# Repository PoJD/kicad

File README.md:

# kicad

Printed circuit boards. A container for all projects, successor to the older
`eagle` repo.

KiCad 10 — text formats, readable diffs, ERC and DRC running in CI through
`kicad-cli` without a GUI. The CI container image tracks the local major
version, because KiCad refuses to open files written by a newer one.

## Boards

| Board | Status | Description |
|---|---|---|
| [`canfuel/`](canfuel/) | design finished, `fab/` generated | fuel consumption converter for a VW PQ34 car, powered from the display it feeds |

The `canfuel` board is finished: schematic and PCB complete, ERC and DRC clean
with zero unconnected items, 24 parts on 55 × 45 mm and two layers, `fab/`
generated and committed. ⚠ **While a fabrication order is outstanding, do not
edit the board files** — `fab/` describes the commit that was sent, and an edit
makes it stop describing what is being made.

The harness is built, fitted and measured —
[`canfuel/docs/harness.md`](canfuel/docs/harness.md) is the procedure. **The
whole build path, across all three repositories, is
[`canfuel/docs/firmware/install.md`](https://github.com/PoJD/canfuel/blob/main/docs/firmware/install.md);**
the steps this repository owns are the board and the loom.

## Prerequisites

| For | What | Notes |
|---|---|---|
| opening and editing | **KiCad 10.x** | the **major** version matters, see below |
| the checks | **`kicad-cli`** | installed with KiCad, no separate download |
| `tools/check-*.py` | **Python 3** | no third-party packages |

```
kicad-cli version          # must print 10.x
```

**The major version is not a preference.** KiCad refuses to open files written
by a newer major version, so a mismatch is a hard failure rather than a
warning. CI runs the `kicad/kicad:10.0` container image and that image tracks
whatever is installed locally — bump the two together, never separately.

Nothing here needs a licence, an account or a plugin. Making the board also
needs no KiCad at all: `fab/` is generated and committed, so a fab house can be
given those files directly.

## Layout

```
lib/                symbols and footprints shared across projects
<board>/
  *.kicad_pro       project
  *.kicad_sch       schematic
  *.kicad_pcb       board
  fab/              gerbers, BOM, CPL — committed
  docs/             design documents, datasheets, and how to build the harness
```

For the `canfuel` board specifically, `canfuel/docs/` holds:

| File | Contents |
|---|---|
| `harness.md` | **making the loom and wiring it into the car** — a checklist, with the crimping, the connector cavities and the fuse |
| `pinout.md` | one-page reference for all three connectors |
| `harness-*.svg` | the connector and the four nets drawn from the real pad coordinates in `canfuel.kicad_pcb`, so they cannot disagree with the board |
| `assembly-orientation.svg` | **the figure to have open while soldering** — both sides of the board, and which way round each of the five parts that can go in backwards goes |
| `solder-check.md` | **after each joint** — for every pad on the board, where the meter must read zero and what it must stay open to, with the gap in millimetres |
| `implementation-plan.md` | how the board was designed, every number cited to a datasheet |
| `*.pdf` | the manufacturers' datasheets, listed in `NOTICE` as theirs |

`*.kicad_prl` is local state and does not belong in the repo (it is gitignored).

`fab/` is committed deliberately even though it is generated: for any board
that has been ordered it must be possible to find out exactly what was sent to
the fab.

## CI

`kicad-cli sch erc` and `kicad-cli pcb drc`. Both must pass before boards are
ordered. The workflow **fails if it finds no design files**, so a green run
always means something was actually opened and checked.

Two project-specific checks run alongside them: `check-netlist.py` and
`check-placement.py`.

## Related repositories

The `canfuel` board is one third of a project that needs all three
repositories. Clone them side by side.

**Building one?** [`canfuel/docs/firmware/install.md`](https://github.com/PoJD/canfuel/blob/main/docs/firmware/install.md)
is the whole path from three clones to a working device, in the order it has to
happen. Making up the harness — the part that lives in this repository — is
step 3 of seven.

| Repository | What it holds | Go there for |
|---|---|---|
| **`kicad`** (this one) | the converter board | the schematic, the PCB, `fab/`, and **`canfuel/docs/harness.md` — how to make the loom and wire it into the car** |
| [`canfuel`](https://github.com/PoJD/canfuel) | the converter firmware | building and flashing the hex, what the LEDs mean, how the car's frames are decoded |
| [`mfd15`](https://github.com/PoJD/mfd15) | the display configuration | the TRI file the display runs and how to upload it |

**The coupling to `canfuel` is the pin assignment**, and it is one-way: the
firmware is written against the board, not the other way round. Changing it
means changing the firmware in the same breath, and invalidates any `fab/`
already sent.

## Licence

[Apache License 2.0](LICENSE). Use it, change it, order the boards, sell them —
the only obligations are to keep the copyright and licence notices and to say
what you changed.

**`NOTICE` lists what is not ours.** The manufacturer datasheets under
`canfuel/docs/` belong to their manufacturers and are redistributed for
reference only; the licence above does not cover them and does not claim to.
Everything else in this repository is covered.

Questions, corrections and pull requests are welcome as issues on any of the
three repositories, or by email to Lubos Housa <luboshousa@gmail.com>.

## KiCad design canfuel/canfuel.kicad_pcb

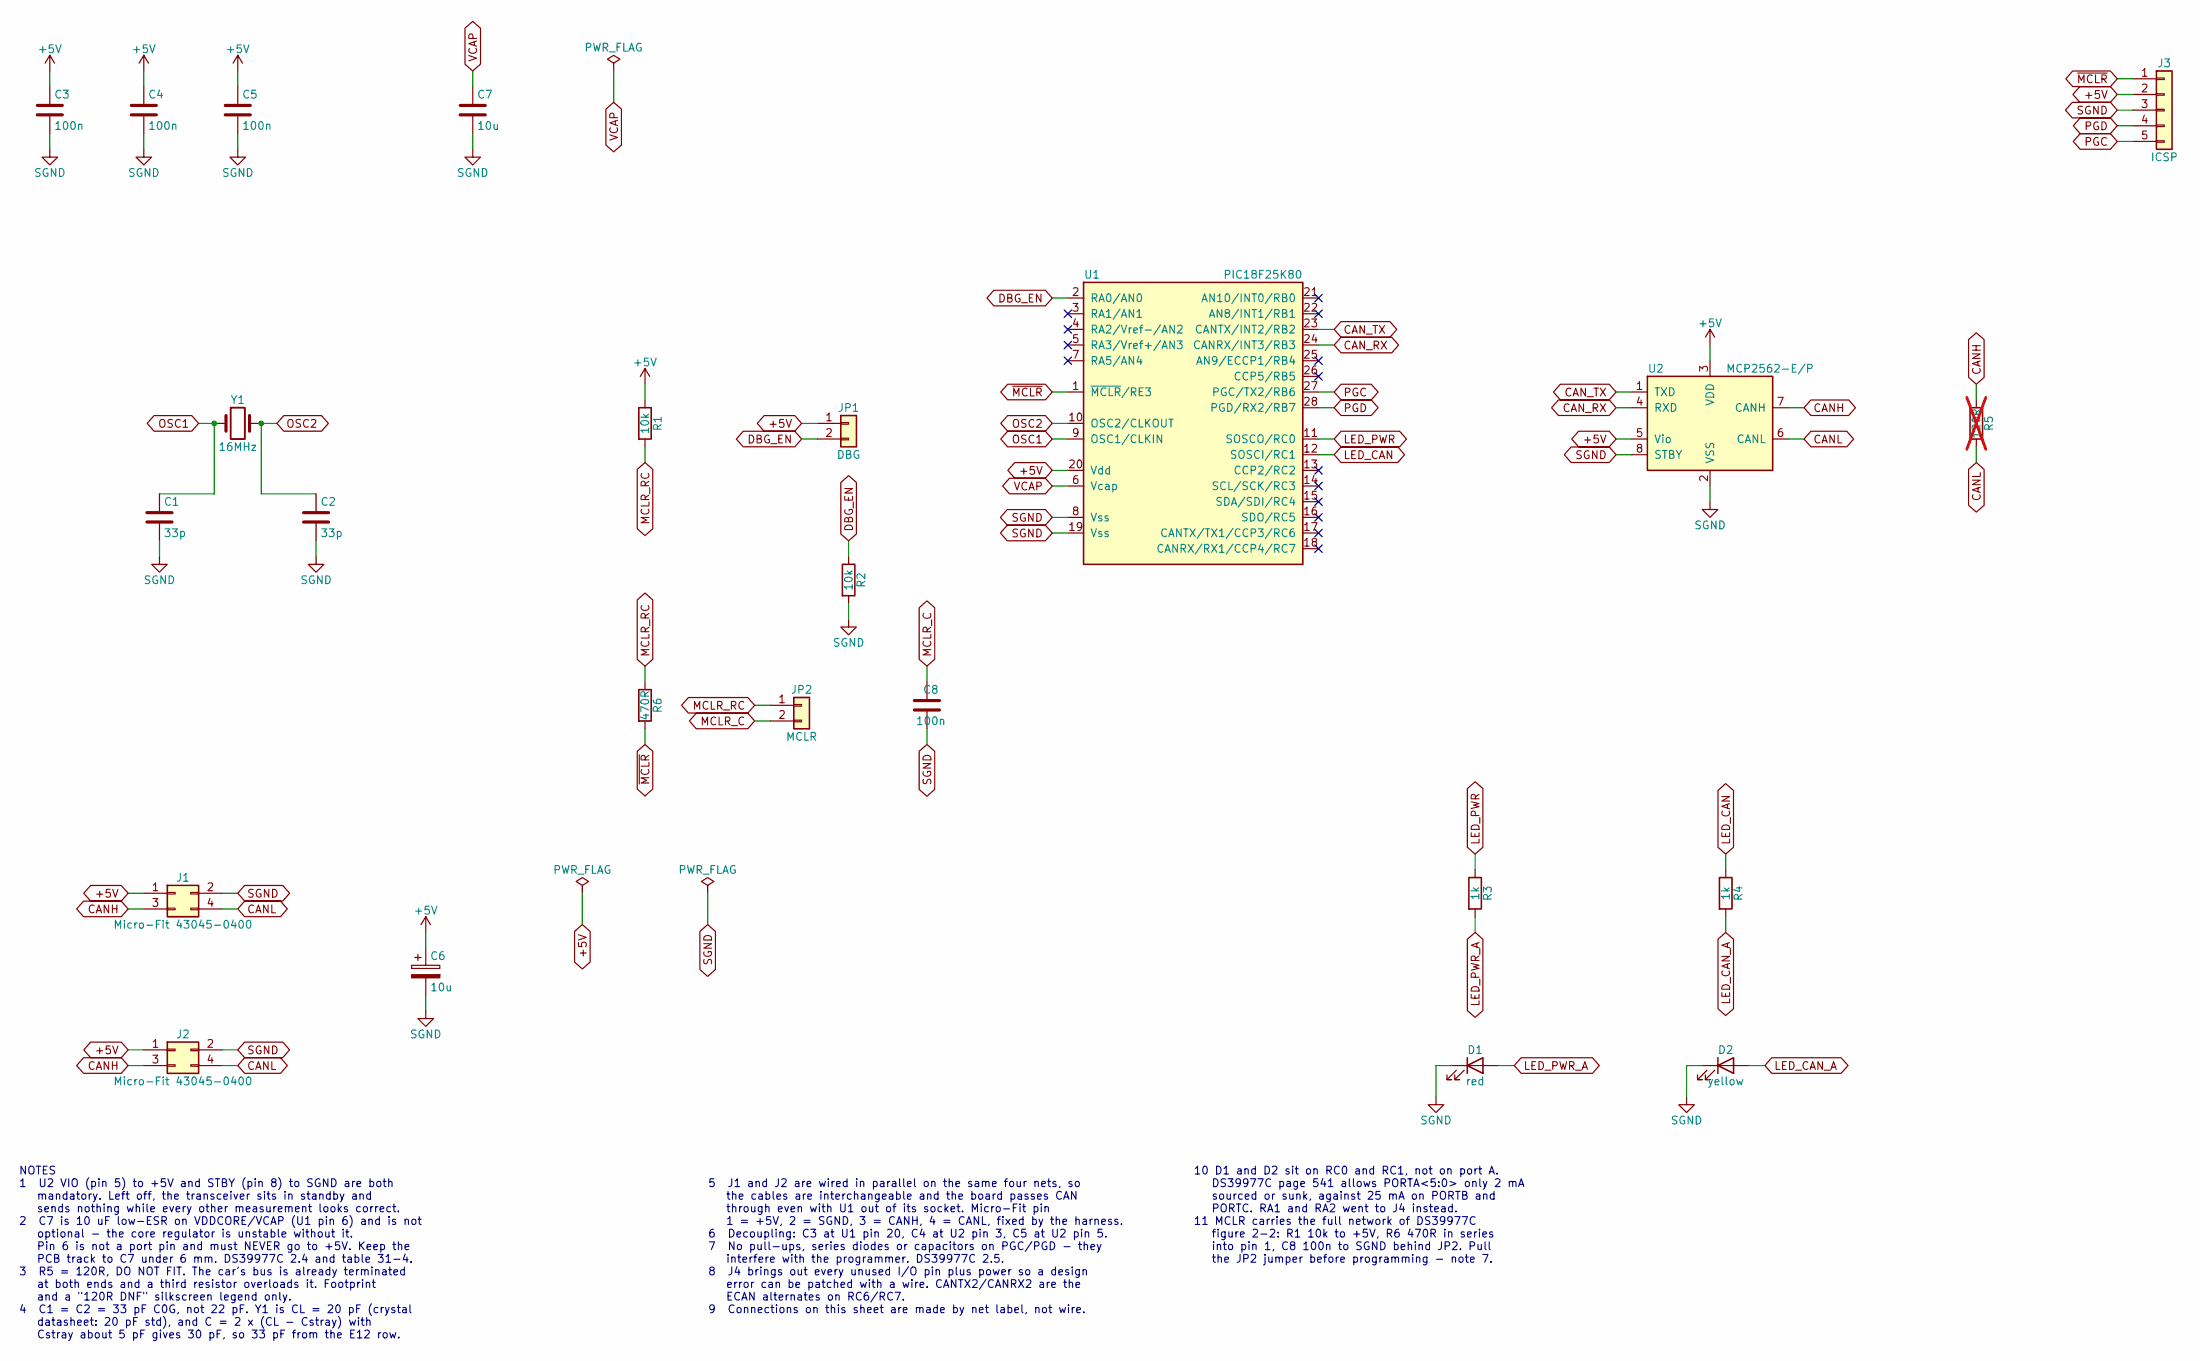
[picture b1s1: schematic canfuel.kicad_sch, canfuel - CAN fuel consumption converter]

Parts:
C1, C2: 33p; C_Disc_D5.0mm_W2.5mm_P5.00mm
C3, C4, C5: 100n; C_Disc_D5.0mm_W2.5mm_P5.00mm
C6: 10u; CP_Radial_D5.0mm_P2.00mm
C7: 10u; C_1210_3225Metric_Pad1.33x2.70mm_HandSolder
C8: 100n; C_Disc_D5.0mm_W2.5mm_P2.50mm
D1: red; LED_D3.0mm
D2: yellow; LED_D3.0mm
J1, J2: Micro-Fit 43045-0400; Molex_Micro-Fit_3.0_43045-0400_2x02_P3.00mm_Horizontal
J3: ICSP; PinHeader_1x05_P2.54mm_Vertical
JP1: DBG; PinHeader_1x02_P2.54mm_Vertical
JP2: MCLR; PinHeader_1x02_P2.54mm_Vertical
R1, R2: 10k; R_Axial_DIN0207_L6.3mm_D2.5mm_P2.54mm_Vertical
R3, R4: 1k; R_Axial_DIN0207_L6.3mm_D2.5mm_P2.54mm_Vertical
R5: 120R; R_Axial_DIN0207_L6.3mm_D2.5mm_P2.54mm_Vertical; not fitted
R6: 470R; R_Axial_DIN0207_L6.3mm_D2.5mm_P2.54mm_Vertical
U1: PIC18F25K80; DIP-28_W7.62mm_Socket
U2: MCP2562-E/P; DIP-8_W7.62mm_Socket
Y1: 16MHz; Crystal_HC49-U_Vertical

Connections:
+5V: C3.1, C4.1, C5.1, C6.1, J1.1, J2.1, J3.2, JP1.1, R1.1, U1.20 (Vdd), U2.3 (VDD), U2.5 (Vio)
CANH: J1.3, J2.3, R5.1, U2.7 (CANH)
CANL: J1.4, J2.4, R5.2, U2.6 (CANL)
CAN_RX: U1.24 (CANRX/INT3/RB3), U2.4 (RXD)
CAN_TX: U1.23 (CANTX/INT2/RB2), U2.1 (TXD)
DBG_EN: JP1.2, R2.1, U1.2 (RA0/AN0)
LED_CAN: R4.1, U1.12 (SOSCI/RC1)
LED_CAN_A: D2.2 (A), R4.2
LED_PWR: R3.1, U1.11 (SOSCO/RC0)
LED_PWR_A: D1.2 (A), R3.2
MCLR_C: C8.1, JP2.2
MCLR_RC: JP2.1, R1.2, R6.1
OSC1: C1.1, U1.9 (OSC1/CLKIN), Y1.1
OSC2: C2.1, U1.10 (OSC2/CLKOUT), Y1.2
PGC: J3.5, U1.27 (PGC/TX2/RB6)
PGD: J3.4, U1.28 (PGD/RX2/RB7)
SGND: C1.2, C2.2, C3.2, C4.2, C5.2, C6.2, C7.2, C8.2, D1.1 (K), D2.1 (K), J1.2, J2.2, J3.3, R2.2, U1.8 (Vss), U1.19 (Vss), U2.2 (VSS), U2.8 (STBY)
VCAP: C7.1, U1.6 (Vcap)
~MCLR: J3.1, R6.2, U1.1 (~MCLR/RE3)

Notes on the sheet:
NOTES 1 U2 VIO (pin 5) to +5V and STBY (pin 8) to SGND are both mandatory. Left off, the transceiver sits in standby and sends nothing while every other measurement looks correct. 2 C7 is 10 uF low-ESR on VDDCORE/VCAP (U1 pin 6) and is not optional - the core regulator is unstable without it. Pin 6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
5 J1 and J2 are wired in parallel on the same four nets, so the cables are interchangeable and the board passes CAN through even with U1 out of its socket. Micro-Fit pin 1 = +5V, 2 = SGND, 3 = CANH, 4 = CANL, fixed by the harness. 6 Decoupling: C3 at U1 pin 20, C4 at U2 pin 3, C5 at U2 pin 5. 7 No 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
10 D1 and D2 sit on RC0 and RC1, not on port A. DS39977C page 541 allows PORTA<5:0> only 2 mA sourced or sunk, against 25 mA on PORTB and PORTC. RA1 and RA2 went to J4 instead. 11 MCLR carries the full network of DS39977C figure 2-2: R1 10k to +5V, R6 470R in series into pin 1, C8 100n to SGND behi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

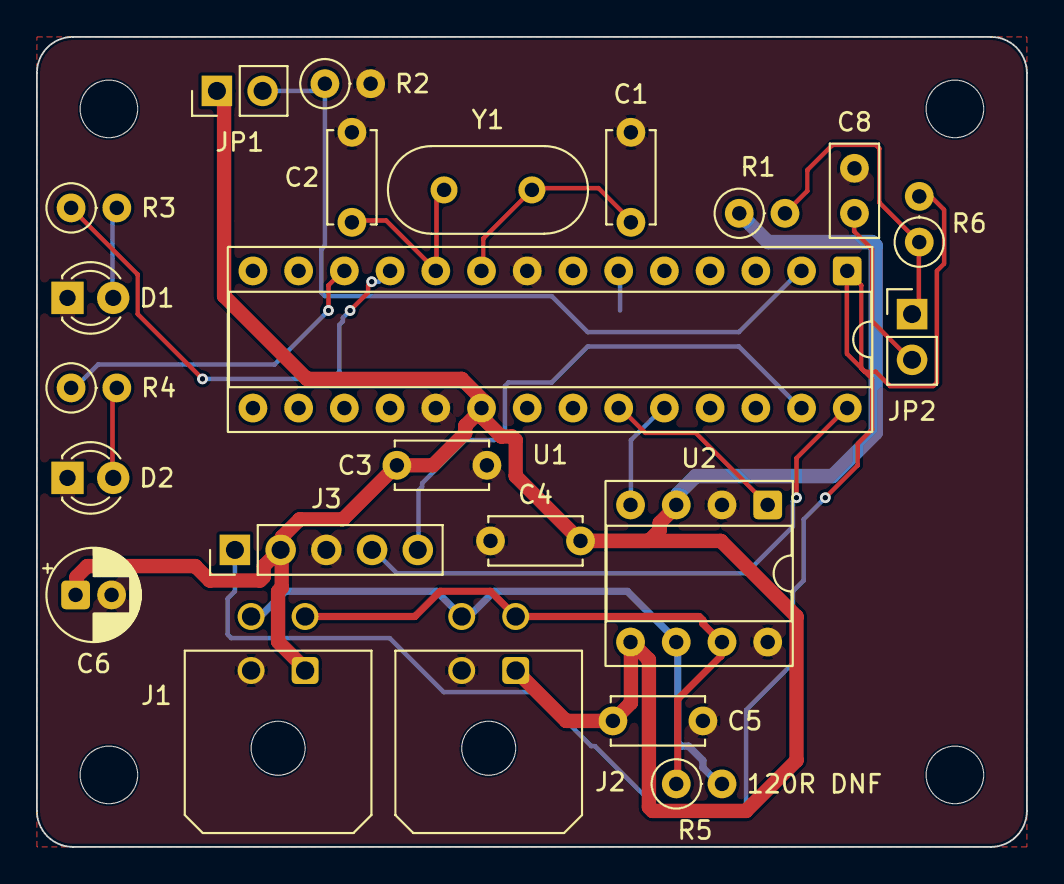
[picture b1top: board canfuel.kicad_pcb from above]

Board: 2 copper layers, 55.0 x 45.0 mm, 28 parts (1 on the bottom side), 19 nets.

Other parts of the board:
H1, H2, H3, H4: MountingHole_3.2mm_M3

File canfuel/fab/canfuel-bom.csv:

"Refs","Value","Footprint","Qty","DNP"
"C1,C2","33p","Capacitor_THT:C_Disc_D5.0mm_W2.5mm_P5.00mm","2",""
"C3-C5","100n","Capacitor_THT:C_Disc_D5.0mm_W2.5mm_P5.00mm","3",""
"C6","10u","Capacitor_THT:CP_Radial_D5.0mm_P2.00mm","1",""
"C7","10u","Capacitor_SMD:C_1210_3225Metric_Pad1.33x2.70mm_HandSolder","1",""
"C8","100n","Capacitor_THT:C_Disc_D5.0mm_W2.5mm_P2.50mm","1",""
"D1","red","LED_THT:LED_D3.0mm","1",""
"D2","yellow","LED_THT:LED_D3.0mm","1",""
"J1,J2","Micro-Fit 43045-0400","Connector_Molex:Molex_Micro-Fit_3.0_43045-0400_2x02_P3.00mm_Horizontal","2",""
"J3","ICSP","Connector_PinHeader_2.54mm:PinHeader_1x05_P2.54mm_Vertical","1",""
"JP1","DBG","Connector_PinHeader_2.54mm:PinHeader_1x02_P2.54mm_Vertical","1",""
"JP2","MCLR","Connector_PinHeader_2.54mm:PinHeader_1x02_P2.54mm_Vertical","1",""
"R1,R2","10k","Resistor_THT:R_Axial_DIN0207_L6.3mm_D2.5mm_P2.54mm_Vertical","2",""
"R3,R4","1k","Resistor_THT:R_Axial_DIN0207_L6.3mm_D2.5mm_P2.54mm_Vertical","2",""
"R6","470R","Resistor_THT:R_Axial_DIN0207_L6.3mm_D2.5mm_P2.54mm_Vertical","1",""
"U1","PIC18F25K80","Package_DIP:DIP-28_W7.62mm_Socket","1",""
"U2","MCP2562-E/P","Package_DIP:DIP-8_W7.62mm_Socket","1",""
"Y1","16MHz","Crystal:Crystal_HC49-U_Vertical","1",""

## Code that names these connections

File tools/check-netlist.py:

#!/usr/bin/env python3
"""Check canfuel's schematic against its implementation plan.

ERC proves the sheet is electrically well formed. It cannot prove that RB2
went to the transceiver's TXD rather than RB3 - both are bidirectional pins
on a two-pin net either way. This does: it exports the netlist and compares
every ref.pin -> net against the tables in canfuel/docs/implementation-plan.md,
which are typed out below by hand.

    python tools/check-netlist.py

Needs kicad-cli on PATH. Exits nonzero on any mismatch, so it can be wired
into CI later if that turns out to be worth it.

When the design changes on purpose, change EXPECT here in the same commit -
that is the point of the file, not an inconvenience.
"""

import os
import subprocess
import sys
import tempfile

HERE = os.path.dirname(os.path.abspath(__file__))
SCH = os.path.join(os.path.dirname(HERE), "canfuel", "canfuel.kicad_sch")

# --------------------------------------------------------------------------
# Expected connections, from canfuel/docs/implementation-plan.md
# --------------------------------------------------------------------------

EXPECT = {}

# Sentinel for a pin that carries a no-connect flag on purpose. KiCad names
# such a net "unconnected-(U1-RA1{slash}AN1-Pad3)", which is generated from the
# pin's own name and would turn this table into a transcription exercise; what
# is actually being asserted is "nothing is wired here, deliberately".
NC = object()

# 4.2 U1 - PIC18F25K80, the full 28-pin table. Pin 6 is VDDCORE/VCAP and pin
# 20 is Vdd; neither is a port pin and the plan says so twice for a reason.
#
# The LEDs are on RC0/RC1, not RA1/RA2: the Absolute Maximum Ratings on
# DS39977C page 541 allow PORTA<5:0> only 2 mA sourced or sunk, against 25 mA
# for PORTB and PORTC. RA1/RA2 took the RC0/RC1 escape slots in exchange, and
# when the escape header itself went (plan 5.4) all fourteen became NC.
for pin, net in {
        1: "~{MCLR}", 2: "DBG_EN", 3: NC, 4: NC, 5: NC,
        6: "VCAP", 7: NC, 8: "SGND", 9: "OSC1", 10: "OSC2",
        11: "LED_PWR", 12: "LED_CAN", 13: NC, 14: NC,
        15: NC, 16: NC, 17: NC, 18: NC,
        19: "SGND", 20: "+5V", 21: NC, 22: NC,
        23: "CAN_TX", 24: "CAN_RX", 25: NC, 26: NC,
        27: "PGC", 28: "PGD"}.items():
    EXPECT["U1.%d" % pin] = net

# 3.1 MCP2562. Pin 5 (Vio) and pin 8 (STBY) are the two that decide whether
# the board transmits at all.
for pin, net in {1: "CAN_TX", 2: "SGND", 3: "+5V", 4: "CAN_RX",
                 5: "+5V", 6: "CANL", 7: "CANH", 8: "SGND"}.items():
    EXPECT["U2.%d" % pin] = net

# 3.2 crystal and its 33 pF loading
EXPECT.update({"Y1.1": "OSC1", "Y1.2": "OSC2",
               "C1.1": "OSC1", "C1.2": "SGND",
               "C2.1": "OSC2", "C2.2": "SGND"})

# 3.3 termination across CANH/CANL, not fitted
EXPECT.update({"R5.1": "CANH", "R5.2": "CANL"})

# 3.4 both Micro-Fit headers on the same four nets
for j in ("J1", "J2"):
    EXPECT.update({j + ".1": "+5V", j + ".2": "SGND",
                   j + ".3": "CANH", j + ".4": "CANL"})

# 3.5 VDDCORE/VCAP, and 4.4 decoupling
EXPECT.update({"C7.1": "VCAP", "C7.2": "SGND"})
for c in ("C3", "C4", "C5", "C6"):
    EXPECT.update({c + ".1": "+5V", c + ".2": "SGND"})

# 4.3a the MCLR network of DS39977C Figure 2-2, in full: the 10k pull-up, the
# 470 ohm that limits what C8 can dump into the pin if MCLR ever breaks down,
# and the jumper that lifts C8 off the node during programming - section 2.5
# is explicit that a capacitor there interferes with the programmer.
EXPECT.update({"R6.1": "MCLR_RC", "R6.2": "~{MCLR}",
               "JP2.1": "MCLR_RC", "JP2.2": "MCLR_C",
               "C8.1": "MCLR_C", "C8.2": "SGND"})

# 4.2 LEDs and the debug jumper
EXPECT.update({"R1.1": "+5V", "R1.2": "MCLR_RC",
               "R2.1": "DBG_EN", "R2.2": "SGND",
               "JP1.1": "+5V", "JP1.2": "DBG_EN",
               "R3.1": "LED_PWR", "R3.2": "LED_PWR_A",
               "R4.1": "LED_CAN", "R4.2": "LED_CAN_A",
               "D1.1": "SGND", "D1.2": "LED_PWR_A",
               "D2.1": "SGND", "D2.2": "LED_CAN_A"})

# 4.3 ICSP
EXPECT.update({"J3.1": "~{MCLR}", "J3.2": "+5V", "J3.3": "SGND",
               "J3.4": "PGD", "J3.5": "PGC"})

# 5.4 escape hatch: REMOVED, see plan 5.4. The fourteen ESC_*
# labels above are now single-node nets and U1's unused pins carry no-connect
# flags. They stay named because the name is what says which pin is which.
#
# Why it went: with J4 fitted the router left 8 of 39 connections unroutable,
# and five of those eight were not escape signals - both status LEDs and the
# whole ICSP header. A header whose job is to rescue a design error was
# stopping the chip being programmed. Without it the board routes complete and
# DRC clean. Patching now means soldering to the PDIP socket pins underneath.

# Section 2 of the plan, less R5's absence from the BOM which is a separate
# check - see plan section 6.
WANT_REFS = {"U1", "U2", "Y1", "C1", "C2", "C3", "C4", "C5", "C6", "C7", "C8",
             "R1", "R2", "R3", "R4", "R5", "R6", "D1", "D2",
             "J1", "J2", "J3", "JP1", "JP2"}

# --------------------------------------------------------------------------


def parse(text):
    """Just enough S-expression reader for a netlist."""
    pos, out = 0, []
    while pos < len(text):
        while pos < len(text) and text[pos] in " \t\r\n":
            pos += 1
        if pos >= len(text):
            break
        node, pos = _node(text, pos)
        out.append(node)
    return out


def _node(text, pos):
    pos += 1  # the opening paren
    items = []
    while True:
        while text[pos] in " \t\r\n":
            pos += 1
        c = text[pos]
        if c == ")":
            return items, pos + 1
        if c == "(":
            node, pos = _node(text, pos)
            items.append(node)
        elif c == '"':
            pos += 1
            buf = []
            while text[pos] != '"':
                if text[pos] == "\\":
                    pos += 1
                buf.append(text[pos])
                pos += 1
            items.append("".join(buf))
            pos += 1
        else:
            start = pos
            while text[pos] not in ' \t\r\n()':
                pos += 1
            items.append(text[start:pos])


def find(node, tag):
    for child in node:
        if isinstance(child, list) and child and child[0] == tag:
            return child
    return None


def find_all(node, tag):
    return [c for c in node if isinstance(c, list) and c and c[0] == tag]


def main():
    sch = sys.argv[1] if len(sys.argv) > 1 else SCH
    if not os.path.exists(sch):
        sys.exit("no such schematic: " + sch)

    with tempfile.TemporaryDirectory() as tmp:
        net = os.path.join(tmp, "canfuel.net")
        subprocess.run(["kicad-cli", "sch", "export", "netlist",
                        "--format", "kicadsexpr", "-o", net, sch],
                       check=True, stdout=subprocess.DEVNULL)
        with open(net, encoding="utf-8") as fh:
            root = parse(fh.read())[0]

    actual = {}
    nets = find(root, "nets")
    for n in find_all(nets, "net"):
        name = find(n, "name")[1]
        for node in find_all(n, "node"):
            actual["%s.%s" % (find(node, "ref")[1], find(node, "pin")[1])] = name

    # The power-flag helpers carry no design intent.
    actual = {k: v for k, v in actual.items()
              if not k.startswith("#PWR") and not k.startswith("#FLG")}

    bad = 0
    for key in sorted(EXPECT, key=lambda k: (k.split(".")[0],
                                             int(k.split(".")[1]))):
        got = actual.get(key, "<not in netlist>")
        want = EXPECT[key]
        if want is NC:
            if not got.startswith("unconnected-"):
                print("MISMATCH %-8s plan says no-connect  netlist says %s"
                      % (key, got))
                bad += 1
        elif got != want:
            print("MISMATCH %-8s plan says %-12s netlist says %s"
                  % (key, want, got))
            bad += 1

    for key in sorted(set(actual) - set(EXPECT)):
        print("UNEXPECTED %-8s -> %s  (not in the plan)" % (key, actual[key]))
        bad += 1

    real = {find(c, "ref")[1]
            for c in find_all(find(root, "components"), "comp")}
    real = {r for r in real if not r.startswith("#")}
    if real != WANT_REFS:
        print("missing refs:   ", sorted(WANT_REFS - real))
        print("unexpected refs:", sorted(real - WANT_REFS))
        bad += 1

    print("%d nets, %d components, %d connections checked"
          % (len(find_all(nets, "net")), len(real), len(EXPECT)))
    print("RESULT: " + ("%d problem(s)" % bad if bad
                        else "schematic matches the implementation plan"))
    return 1 if bad else 0


if __name__ == "__main__":
    sys.exit(main())
